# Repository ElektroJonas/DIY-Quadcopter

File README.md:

# Quadcopter Built from Scratch

This project contains all the materials used in building a quadcopter drone. It was part of a project course in electrical engineering and embedded systems at Uppsala University, where we spent a portion of the semester designing and constructing a quadcopter from scratch using off-the-shelf components and some interesting control algorithms! 🚀

### Project Demonstration and Summary
- A fun summary of the project's development can be found here: [YouTube Summary](https://youtu.be/-V470g73WhM?si=RAoppi26RXBP144A)  
- A demonstration of the drone can be found here: [YouTube Demonstration](https://youtu.be/1-YmHmeVQKA?si=Rilc_he6dhYzZJqS)  

### Final Result
Below is a figure of the completed drone and its custom-built remote control:

| Drone | Remote |  
| --- | --- |  
|  |  |

### Control System  
The control system consists of two main components: **Attitude Control** and **Altitude Control**.  Note: Altitude control was not used in the final version of the drone since we didnt get it to work well enough.

- **Attitude Control** (angle relative to the ground plane) is implemented using a cascaded PID controller with a Kalman filter and an internal rate control loop. It relies on a low-cost MEMS sensor (gyroscope/accelerometer) for angle estimation.  
- **Altitude Control** is managed using a pressure sensor in combination with the MEMS sensor for attitude estimation, supplemented by a Zero Velocity Update (ZUPT) algorithm for improved stability and accuracy.   

The control system was implemented on an ESP32 microcontroller, utilizing the ESP-NOW protocol for wireless communication.

### Full Project Report
A detailed description of this project, including development insights, sources, and useful references for anyone interested in building their own drone, can be found in **Quadcopter_final_report.pdf**.

### Acknowledgments  
We would like to express our gratitude to [CarbonAeronautics](https://github.com/CarbonAeronautics) for providing valuable resources that greatly aided the early development of this project.  

A special thanks to **Uppsala University** for sponsoring the project and providing the opportunity to bring this idea to life!

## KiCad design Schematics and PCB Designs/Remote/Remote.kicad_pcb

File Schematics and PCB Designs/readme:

The quadcopter has a schematic but currently no pcb design as it was realised on a experimental board. 
The remote has a schematic and pcb design. The pcb design can be improved further by adding 100nF capacitors on the ADC inputs to filter out noise

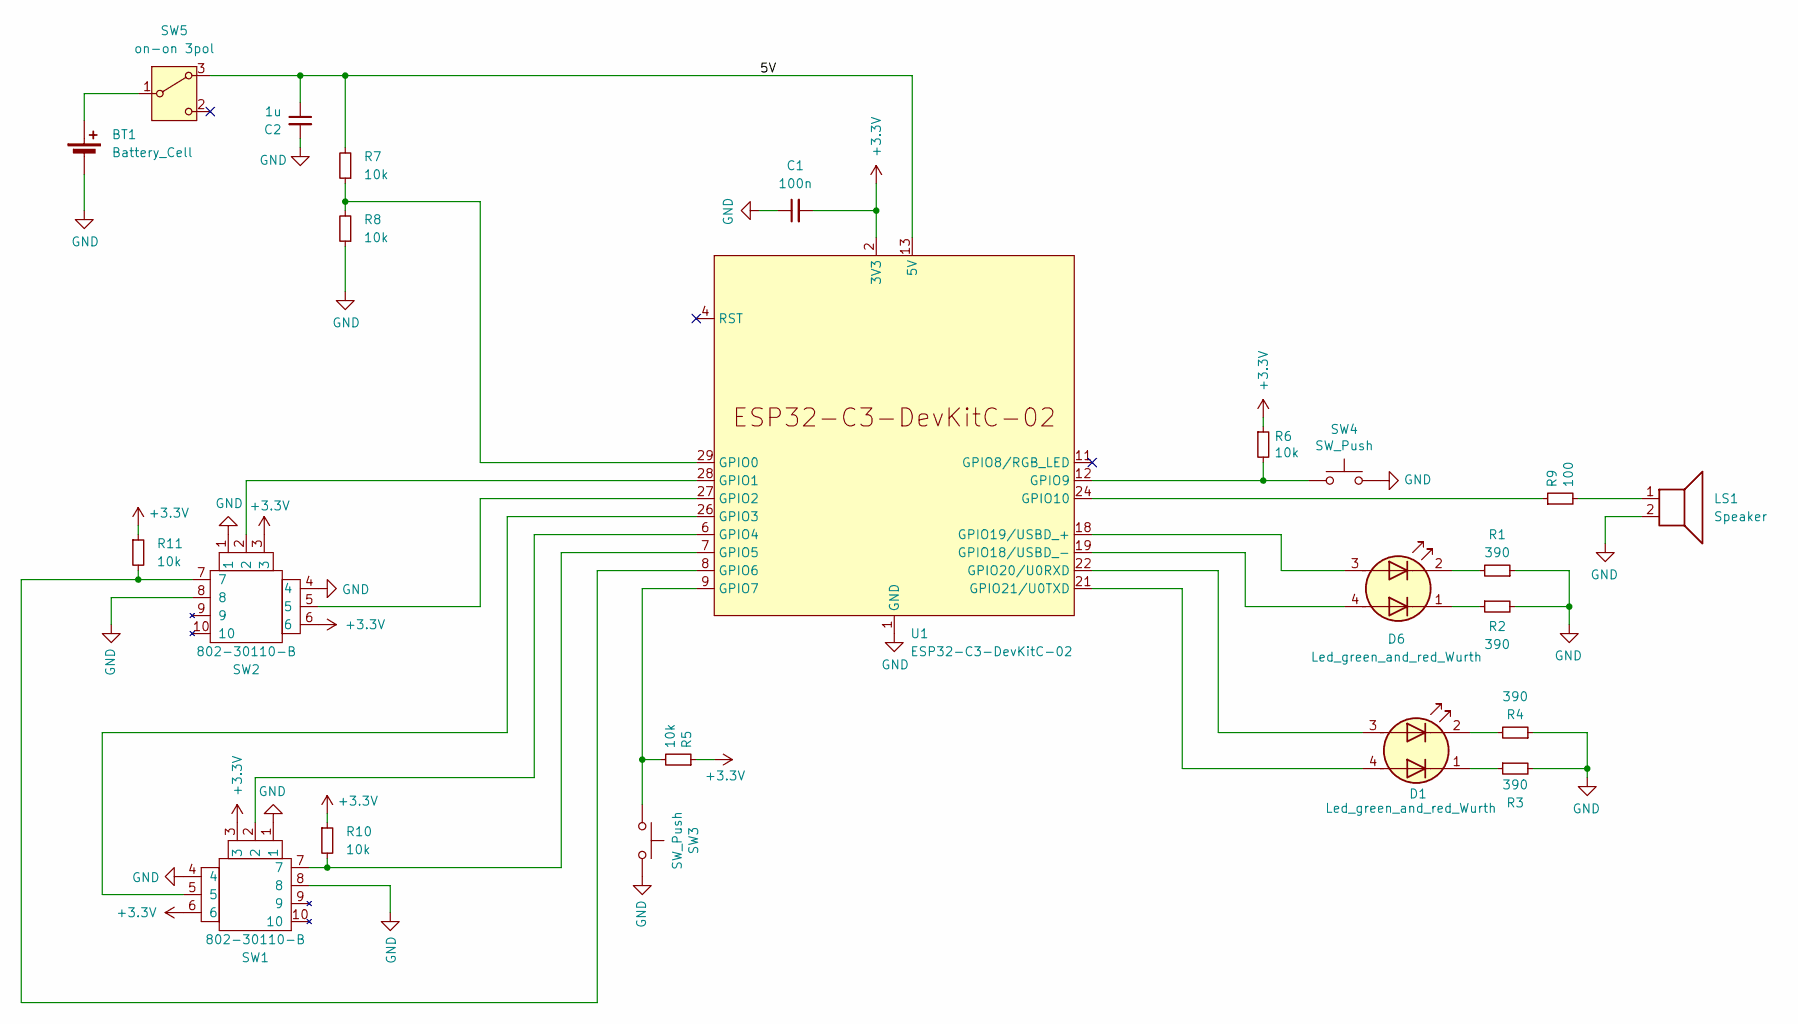
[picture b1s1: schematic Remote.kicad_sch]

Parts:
BT1: Battery_Cell; Batterihållare 4xAAA
C1: 100n; C_1206_3216Metric_Pad1.33x1.80mm_HandSolder
C2: 1u; C_1206_3216Metric_Pad1.33x1.80mm_HandSolder
D1, D6: Led_green_and_red_Wurth; Led green and red Wurth
LS1: Speaker; summer 4khz miniatyr
R1, R2, R3, R4: 390; R_1206_3216Metric_Pad1.30x1.75mm_HandSolder
R5, R6, R7, R8, R10, R11: 10k; R_1206_3216Metric_Pad1.30x1.75mm_HandSolder
R9: 100; R_1206_3216Metric_Pad1.30x1.75mm_HandSolder
SW1, SW2: 802-30110-B; Joystick
SW3, SW4: SW_Push; SW_PUSH-12mm
SW5: on-on 3pol; Skjutomkopplare 1-pol on-on pcb vinklad
U1: ESP32-C3-DevKitC-02

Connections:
5V: C2.1, R7.2, SW5.3 (A), U1.13 (5V), U1.14 (5V)
+3.3V: C1.2, R5.1, R6.1, R10.1, R11.1, SW1.3, SW1.6, SW2.3, SW2.6, U1.2 (3V3), U1.3 (3V3)
GND: BT1.2 (-), C1.1, C2.2, LS1.2, R1.1, R2.2, R3.2, R4.1, R8.1, SW1.1, SW1.4, SW1.8, SW2.1, SW2.4, SW2.8, SW3.2, SW4.2, U1.1 (GND), U1.5 (GND), U1.10 (GND), U1.15 (GND), U1.16 (GND), U1.17 (GND), U1.20 (GND), U1.23 (GND), U1.25 (GND), U1.30 (GND)
unnamed: BT1.1 (+), SW5.1 (B)
unnamed: D1.3 (A1), U1.22 (GPIO20/U0RXD)
unnamed: D1.4 (A2), U1.21 (GPIO21/U0TXD)
unnamed: D1.2 (K1), R4.2
unnamed: D1.1 (K2), R3.1
unnamed: D6.3 (A1), U1.18 (GPIO19/USBD_+)
unnamed: D6.4 (A2), U1.19 (GPIO18/USBD_-)
unnamed: D6.2 (K1), R1.2
unnamed: D6.1 (K2), R2.1
unnamed: LS1.1, R9.2
unnamed: R7.1, R8.2, U1.29 (GPIO0)
unnamed: SW2.2, U1.28 (GPIO1)
unnamed: SW2.5, U1.27 (GPIO2)
unnamed: SW1.5, U1.26 (GPIO3)
unnamed: SW1.2, U1.6 (GPIO4)
unnamed: R10.2, SW1.7, U1.7 (GPIO5)
unnamed: R11.2, SW2.7, U1.8 (GPIO6)
unnamed: R5.2, SW3.1, U1.9 (GPIO7)
unnamed: R6.2, SW4.1, U1.12 (GPIO9)
unnamed: R9.1, U1.24 (GPIO10)

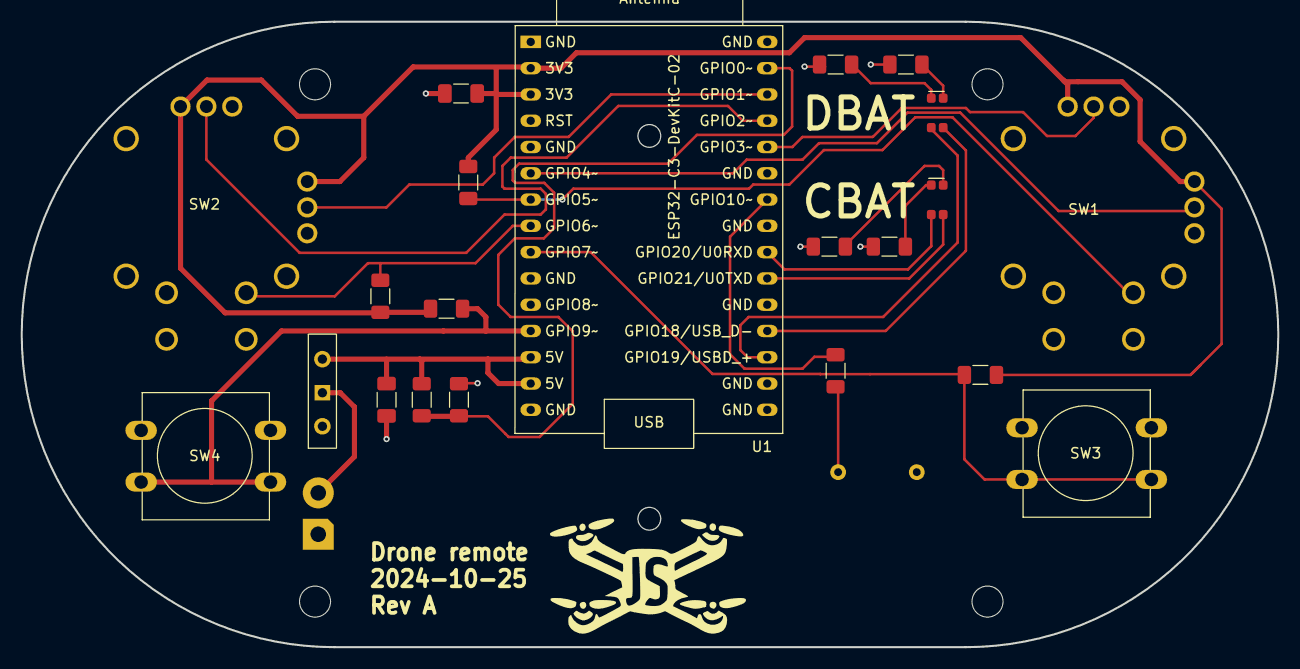
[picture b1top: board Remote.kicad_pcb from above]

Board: 2 copper layers, 121.5 x 60.5 mm, 23 parts (1 on the bottom side), 23 nets.

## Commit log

2025-01-08 Create Quadcopter_Cascaded_PID_Control_Kalman.ino
    Complete code to control a esp32 based quadcopter is inserted.
2025-01-08 Moved file into folder for easier navigation
2025-01-08 Uploaded Schematics and PCB Designs
    Uploaded schematics for the quadcopter and remote, as well as a pcb design for the remote. The quadcopter does not yet have a custom made pcb.
2025-01-08 Added arduino code for the remote control aswell as a components list
2025-01-08 Pictures and updated README
2025-01-16 Small changes
2025-03-12 Create Cad files
    Added link to onshape cad files for drone frame and remote
